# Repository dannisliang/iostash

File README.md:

ioStash - Redefining IoT Ecosystem
========================================

About
-----
ioStash is a completely hackable advanced IoT eco system unlike any other, featuring data mining from the collected data, real-time multi channel data streaming, easy access to data API's, remote configuration of hardware modules and more.

ioStash eco system consists of an open IoT module with built in Wifi (and/or ethernet), I/O pin host, built in battery and a cloud based data repository to collect data. Any number of IoT Modules can be used to segregate and process data from multiple locations. Requiring minimum effort to configure and starting up within minutes, Yes you heard it right, minutes! ioStash is the perfect solution to those wasted hours on setting up and configuring.

How is this different from x ?
-----
ioStash is a full fledged IoT eco system with a hardware data logger and a cloud based dashboard. The hardware part of ioStash is powerful enough to sample 3 analog and 3 digital signals simultaneously and also supports sensors using I2C and SPI communication protocols.

ioStash dashboard lets you analyze and re-stream data to multiple channels and also lets you configure your hardware remotely. It even lets you find complex patterns and anomalies from your data!

The best part is, ioStash is cheap! Infact, it is the cheapest IoT platform on the planet!

Current State
-------------
ioStash is currently under extensive development and is currently under closed beta. If you'd like to contribute, please feel free to contact us at support@iostash.com or create a pull request on the available sources in this repo. Since the project is still in its infancy, all of the project sources are not in this repo, if you'd like to tinker with the code, please drop a mail and we'll let you in!

for all queries, please drop a mail to support@iostash.com

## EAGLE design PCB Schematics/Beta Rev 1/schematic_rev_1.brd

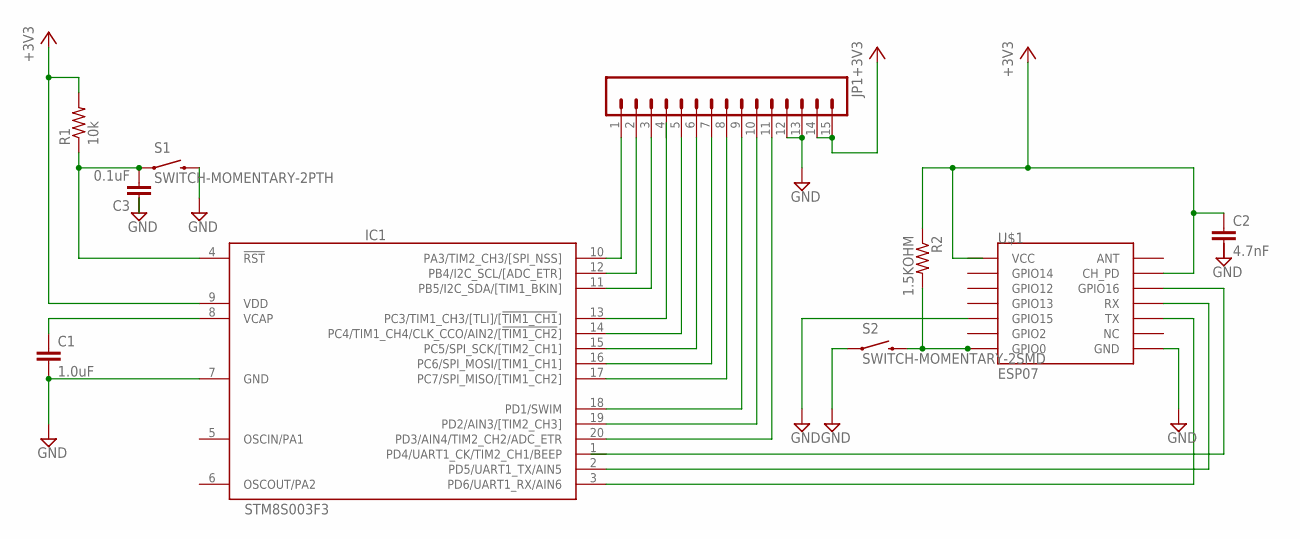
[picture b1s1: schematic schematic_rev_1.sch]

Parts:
C1: 1.0uF; 0402-CAP
C2: 4.7nF; 0603-CAP
C3: 0.1uF; 0402-CAP
IC1: STM8S003F3; TSSOP20
JP1: M15; 1X15
R1: 10k; AXIAL-0.3
R2: 1.5KOHM; 0603
S1: SWITCH-MOMENTARY-2PTH; TACTILE-PTH
S2: SWITCH-MOMENTARY-2SMD; TACTILE-SWITCH-SMD
U$1: ESP07

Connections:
+3V3: C2.1, IC1.9 (VDD), JP1.14, JP1.15, R1.P$2 (2), R2.1, U$1.CH_PD
GND: C1.2, C3.1, IC1.7 (GND), JP1.12, JP1.13, S1.3 (2), S2.1, U$1.GND, U$1.GPIO15
unnamed: C1.1, IC1.8 (VCAP)
unnamed: IC1.2 (PD5/UART1_TX/AIN5), U$1.RX
unnamed: IC1.10 (PA3/TIM2_CH3/[SPI_NSS]), JP1.1
unnamed: IC1.3 (PD6/UART1_RX/AIN6), U$1.TX
unnamed: IC1.12 (PB4/I2C_SCL/[ADC_ETR]), JP1.2
unnamed: IC1.11 (PB5/I2C_SDA/[TIM1_BKIN]), JP1.3
unnamed: IC1.13 (PC3/TIM1_CH3/[TLI]/[!TIM1_CH1!]), JP1.4
unnamed: IC1.14 (PC4/TIM1_CH4/CLK_CCO/AIN2/[!TIM1_CH2!]), JP1.5
unnamed: IC1.15 (PC5/SPI_SCK/[TIM2_CH1]), JP1.6
unnamed: IC1.16 (PC6/SPI_MOSI/[TIM1_CH1]), JP1.7
unnamed: IC1.17 (PC7/SPI_MISO/[TIM1_CH2]), JP1.8
unnamed: IC1.18 (PD1/SWIM), JP1.9
unnamed: IC1.19 (PD2/AIN3/[TIM2_CH3]), JP1.10
unnamed: IC1.20 (PD3/AIN4/TIM2_CH2/ADC_ETR), JP1.11
unnamed: C3.2, IC1.4 (!RST), R1.P$1 (1), S1.1
unnamed: R2.2, S2.3 (2), U$1.GPIO0

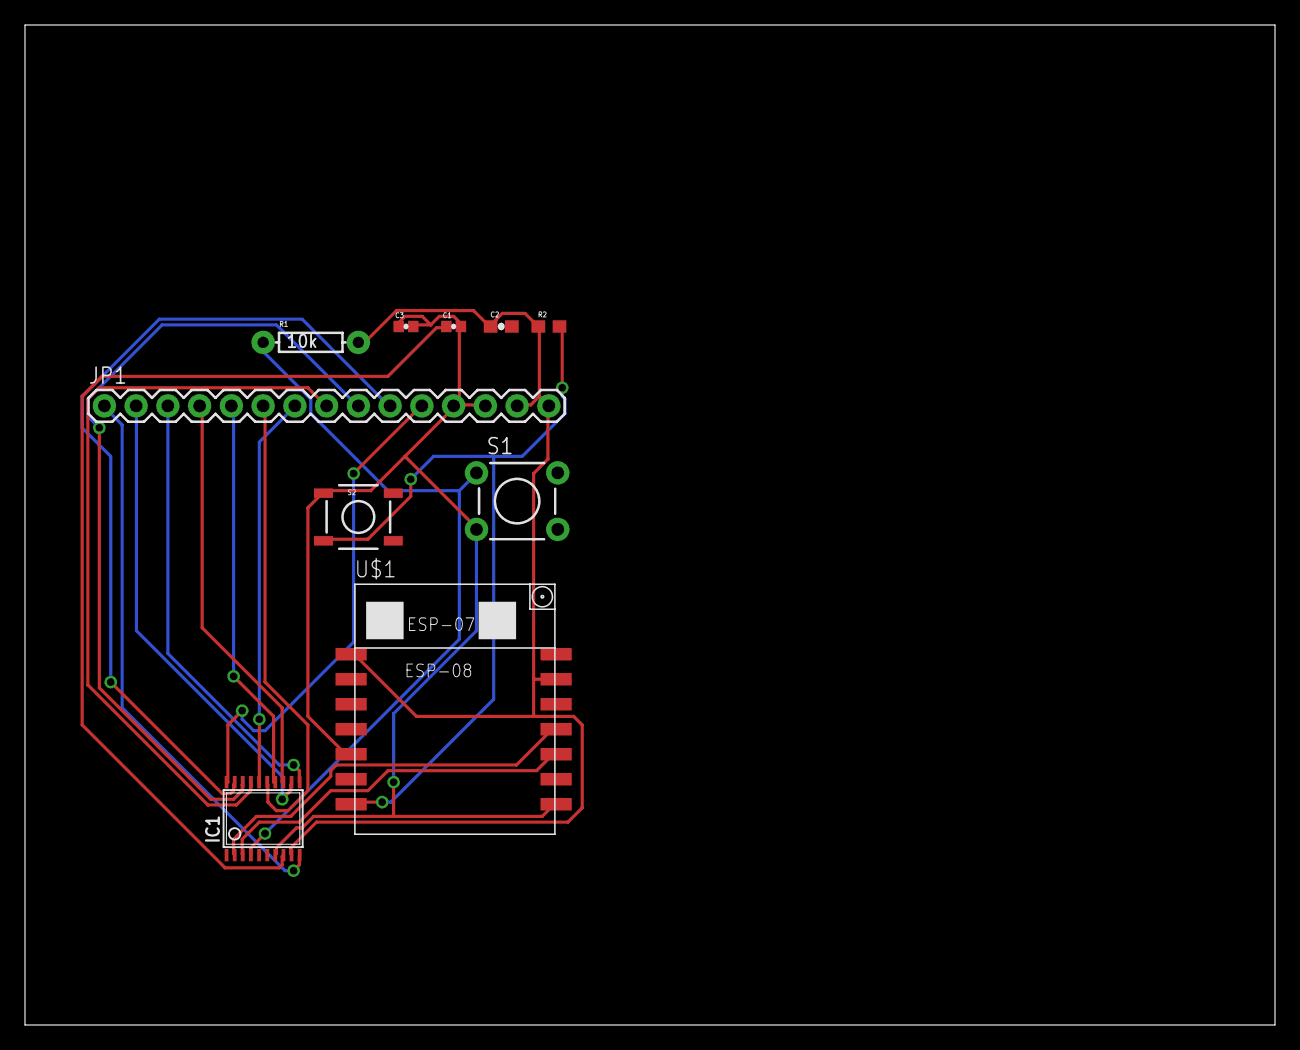
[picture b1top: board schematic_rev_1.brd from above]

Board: 2 copper layers, 100.0 x 80.0 mm, 10 parts (0 on the bottom side), 18 nets.

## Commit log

2015-07-18 Initial commit, includes beta revision 1 PCB files in eagle format
2015-07-19 Updated schematic by Manivannan. Corrected component placements and cleaned up the nets.

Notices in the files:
parts and their libraries:
SparkFun-Capacitors: Licensing: Creative Commons ShareAlike 4.0 International - https://creativecommons.org/licenses/by-sa/4.0
